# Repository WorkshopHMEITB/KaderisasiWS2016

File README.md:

# KaderisasiWS2016
###Repository untuk keperluan calon kru WS HME ITB 2016
1. **Informasi Umum**
  * Presentasi dan spesifikasi tugas tiap day dapat dilihat pada folder day yang bersesuaian
  * Pembagian kelompok beserta mentor-mentornya dapat dilihat [disini](https://github.com/WorkshopHMEITB/KaderisasiWS2016/blob/master/KelompokCakruWS2016.csv)
  * Kontak mentor dapat dilihat [disini](https://github.com/WorkshopHMEITB/KaderisasiWS2016/blob/master/KontakMentorCakruWS2016.csv)
2. **Aturan umum pengumpulan tugas**
  * Tugas yang sudah selesai harus dipresentasikan kepada mentor masing-masing kelompok pada waktu yang ditentukan bersama mentor sebelum batas waktu yang diberikan pada spesifikasi tugas
  * Tugas harus disertai dengan dokumentasi tugas menggunakan template dokumentasi yang ada pada repository KaderisasiWS2016
  * File-file terkait (yang akan diberitahu pada spesifikasi tiap tugas) beserta dokumentasinya harus dikumpulkan melalui repository KaderisasiWS2016 sebelum batas waktu yang diberikan pada spesifikasi tugas (cara pengumpulan tugas ke repository ada pada poin 3 file ini)
  * Telat mempresentasikan kepada mentor akan mengakibatkan pengurangan nilai total sebesar 5% (telat 1 hari), 15% (telat 2 hari), 30% (telat 3 hari), dan 50% (dengan kata lain tidak dianggap mengumpulkan jika telat lebih dari 4 hari)
3. **Cara pengumpulan tugas**<br  />
 1. Jika anda belum terdaftar di github, klik tombol ***Sign up*** di pojok kanan atas [page ini](https://github.com/WorkshopHMEITB/KaderisasiWS2016) dan ikuti terus prosedurnya hingga anda terdaftar
 2. Jika anda sudah terdaftar, *sign in* dengan menekan tombol ***Sign in*** di pojok kanan atas [page ini](https://github.com/WorkshopHMEITB/KaderisasiWS2016)
 3. Klik tombol ***Fork*** di pojok kanan atas [page ini](https://github.com/WorkshopHMEITB/KaderisasiWS2016)
 4. *Pop up window* akan muncul setelah anda menekan tombol *Fork*, tekan ***profil anda***.
 5. Sekarang, *repository* baru (yang merupakan *forked* repository [WorkshopHMEITB/KaderisasiWS2016](https://github.com/WorkshopHMEITB/KaderisasiWS2016)) akan muncul di profil anda. Alamat repository tersebut akan berbentuk seperti ini: https://github.com/USER_NAME/KaderisasiWS2016, sebagai contoh, https://github.com/fuad1502/KaderisasiWS2016. (Jika anda baru saja mem-*fork* repository WorkshopHMEITB/KaderisasiWS2016, anda akan langsung ter-*redirect* ke alamat repository baru anda tersebut)
 6. Setelah *forked repository* berhasil anda buat, anda dapat ***mengupload file-file*** yang harus anda upload ke repository tersebut. Cara mengupload file yang baik dan benar, ada pada bagian 4, "Cara mengupload file-file ke forked repository"
 7. Setelah semua file yang diperlukan sudah anda upload, tekan ***New Pull Request***
 8. Kemudian tekan tombol ***Create pull request***. Tuliskan "Tugas Day X Kelompok Y" pada bagian title dan tekan kembali tombol ***Create pull request***
 9. Selesai. Jika anda sudah mengupload semua file dengan benar, pihak kami akan menerima *pull request* anda dan menggabungkannya ke dalam repository [WorkshopHMEITB/KaderisasiWS2016](https://github.com/WorkshopHMEITB/KaderisasiWS2016)
4. **Cara mengupload file-file ke forked repository**
 1. Buka *forked repository* anda di https://github.com/USER_NAME/KaderisasiWS2016
 2. Buka folder day yang bersesuaian
 3. Buat folder pengumpulan tugas kelompok anda di dalam folder day tersebut dengan cara sebagai berikut
     * Tekan tombol ***Create new file***
     * Pada bagian "Name your file...", tulis "KelompokX" (ganti X dengan nomor kelompok anda), lalu tekan "/". Kemudian, tulis lagi ".gitkeep"
     * *Scroll* kebawah dan klik ***Commit new file***
 4. Pada folder pengumpulan tugas kelompok anda tersebut, klik tombol ***Upload files***
 5. Klik ***choose your files*** dan pilih file mana saja yang ingin anda upload
 6. Setelah semua file berhasil diupload, tekan tombol ***Commit changes***

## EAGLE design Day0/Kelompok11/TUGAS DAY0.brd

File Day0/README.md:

#Tugas Day 0
###*Template file dokumentasi belum ada, kerjakan saja file skematik dan PCB nya dahulu*
###*Tugas PCB file dan schematic file harus dikerjakan setiap anggota kelompok, namun PCB yang perlu dicetak hanya satu per kelompok*
1. **Detail Tugas**
  1. Membuat file skematik dari rangkaian di bawah ini menggunakan software Eagle<br  />
  
  2. Membuat file PCB dari skematik yang telah dibuat menggunakan software Eagle
  3. Mencetak 1 buah PCB dari file PCB yang telah dibuat
  4. Membeli komponen-komponen yang dibutuhkan dan memasangnya/menyoldernya pada PCB yang telah dicetak
  5. Membuat dan mengupload file dokumentasi ke folder yang sesuai di repository [KaderisasiWS2016](https://github.com/WorkshopHMEITB/KaderisasiWS2016) (caranya dapat dilihat pada file [README.md](https://github.com/WorkshopHMEITB/KaderisasiWS2016/blob/master/README.md) pada root directory repository)
  6. Mengupload file-file terkait ke folder yang sesuai di repository [KaderisasiWS2016](https://github.com/WorkshopHMEITB/KaderisasiWS2016). File-file yang dimaksud ialah sebagai berikut.
    * File Skematik
    * File PCB
2. **Parameter Penilaian**<br  />
Coming soon...
3. **Deadline**<br  />
Sabtu 17/9/2016 (Namun mengumpulkan minggu tidak dihitung telat satu hari untuk tugas ini, dikarenakan PCB tidak mungkin selesai hari minggu)
4. **Informasi Tambahan**
  * Software Eagle dapat didownload secara gratis sebagai *freeware* dari https://cadsoft.io/
  * Rangkaian yang diberikan diatas sulit untuk dimengerti dikarenakan pengintegrasian 4 komponen transistor dalam rangkaian kedalam satu IC CA3046. Berikut adalah gambar skematik rangkaian diatas apabila keempat transistor digambarkan satu per satu. <br  />
  
  * Tips untuk Mempermudah Pengerjaan
    * Manfaatkan fitur DRC pada pembuatan file PCB untuk memastikan desain yang anda buat dapat dicetak oleh tempat pencetakan anda
    * Gunakan ground plane untuk mempermudah routing (Tidak harus)
    * Gunakan IC header untuk memastikan IC tidak akan rusak saat proses penyolderan, serta agar IC dapat dilepas untuk dipakai dalam hal lain (Tidak harus)
    * Untuk mengurangi biaya mencetak PCB, ketika ingin mencetak, cetak PCB beberapa kelompok secara bersama-sama
    * Cetak maksimal 3 hari sebelum deadline jika pakai masking (Kamis, 15/9/2016), 2 hari jika tidak. Untuk jaga-jaga.
  * Informasi Pencetakan PCB
    * *Spectra* 
      * Lokasi : https://goo.gl/maps/9tBonaAyMZR2
      * Email : kng@bdg.centrin.net.id
      * Telepon : 022 - 7322667
      * Teknologi : Ukuran jalur minimum 0.2 mm (kalau mau aman 0.25 mm)
      * Dapat mencetak langsung ke tempatnya dengan membawa file PCB, atau dapat melalui email dan transfer ATM
    * *MultiKarya* 
      * Lokasi : https://goo.gl/maps/EgyCBrZe8uH2
      * Website : www.multikarya.com
      * Email : pcb_multikarya@yahoo.com
      * Telepon : 022 - 720 2852
      * Teknologi : lihat lengkapnya di http://www.multikarya.com/pcb_technical_indonesia.html
    * *Selc* 
      * Lokasi : https://goo.gl/maps/5XCbfng3uKE2
      * Website : www.selc-komponen.co.id
      * Email : selc@bdg.centrin.net.id
      * Telepon : 022 - 721 0909
      * Teknologi : lihat lengkapnya di http://www.selc-komponen.co.id/index.php?route=information/information&information_id=7)
  * Informasi Pembelian Komponen
    * *Anam* (https://goo.gl/maps/y4qWtzdkQtB2 sebelah Balubur Town Square)
    * *Jaya Plaza* (https://goo.gl/maps/nTADkQ1KY322)<br  />
    Jika kesulitan dalam menemukan CA3046, dapat ditemukan di toko i.want.electronics di Jaya Plaza dengan harga Rp. 27500
    * *Duta Irama* (https://goo.gl/maps/VzKpAT1tsW42 depan Jaya Plaza)
  * Jika ada pertanyaan silakan hubungi [mentor masing-masing](https://github.com/WorkshopHMEITB/KaderisasiWS2016/blob/master/KontakMentorCakruWS2016.csv)

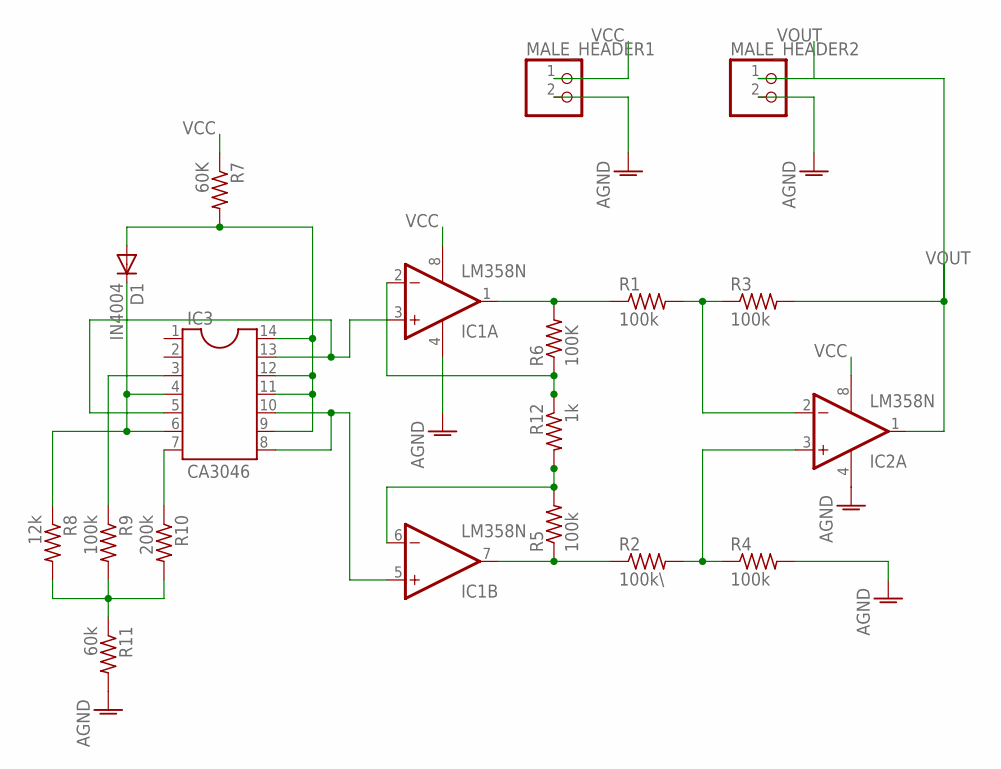
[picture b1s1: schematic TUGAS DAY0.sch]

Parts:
D1: IN4004; D-7.5
IC1, IC2: LM358N; DIL08
IC3: CA3046; DIL14
MALE_HEADER1, MALE_HEADER2: PINHD-1X2; 1X02
R1, R3, R4, R5, R9: 100k; 0207/7
R2: 100k\; 0207/7
R6: 100K; 0207/7
R7: 60K; 0207/7
R8: 12k; 0207/7
R10: 200k; 0207/7
R11: 60k; 0207/7
R12: 1k; 0207/7

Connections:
AGND: IC1.4 (V-), IC2.4 (V-), MALE_HEADER1.2, MALE_HEADER2.2, R4.2, R11.2
unnamed: IC1.6 (-IN), R5.2, R12.2
unnamed: D1.A, IC3.9, IC3.11, IC3.12, IC3.14, R7.2
unnamed: R8.2, R9.2, R10.2, R11.1
unnamed: IC3.7, R10.1
unnamed: IC3.3, R9.1
unnamed: D1.C, IC3.4, IC3.6, R8.1
unnamed: IC1.3 (+IN), IC3.5, IC3.13
unnamed: IC1.5 (+IN), IC3.8, IC3.10
unnamed: IC1.1 (OUT), R1.1, R6.2
unnamed: IC1.2 (-IN), R6.1, R12.1
unnamed: IC1.7 (OUT), R2.1, R5.1
unnamed: IC2.3 (+IN), R2.2, R4.1
unnamed: IC2.2 (-IN), R1.2, R3.1
VCC: IC1.8 (V+), IC2.8 (V+), MALE_HEADER1.1, R7.1
VOUT: IC2.1 (OUT), MALE_HEADER2.1, R3.2

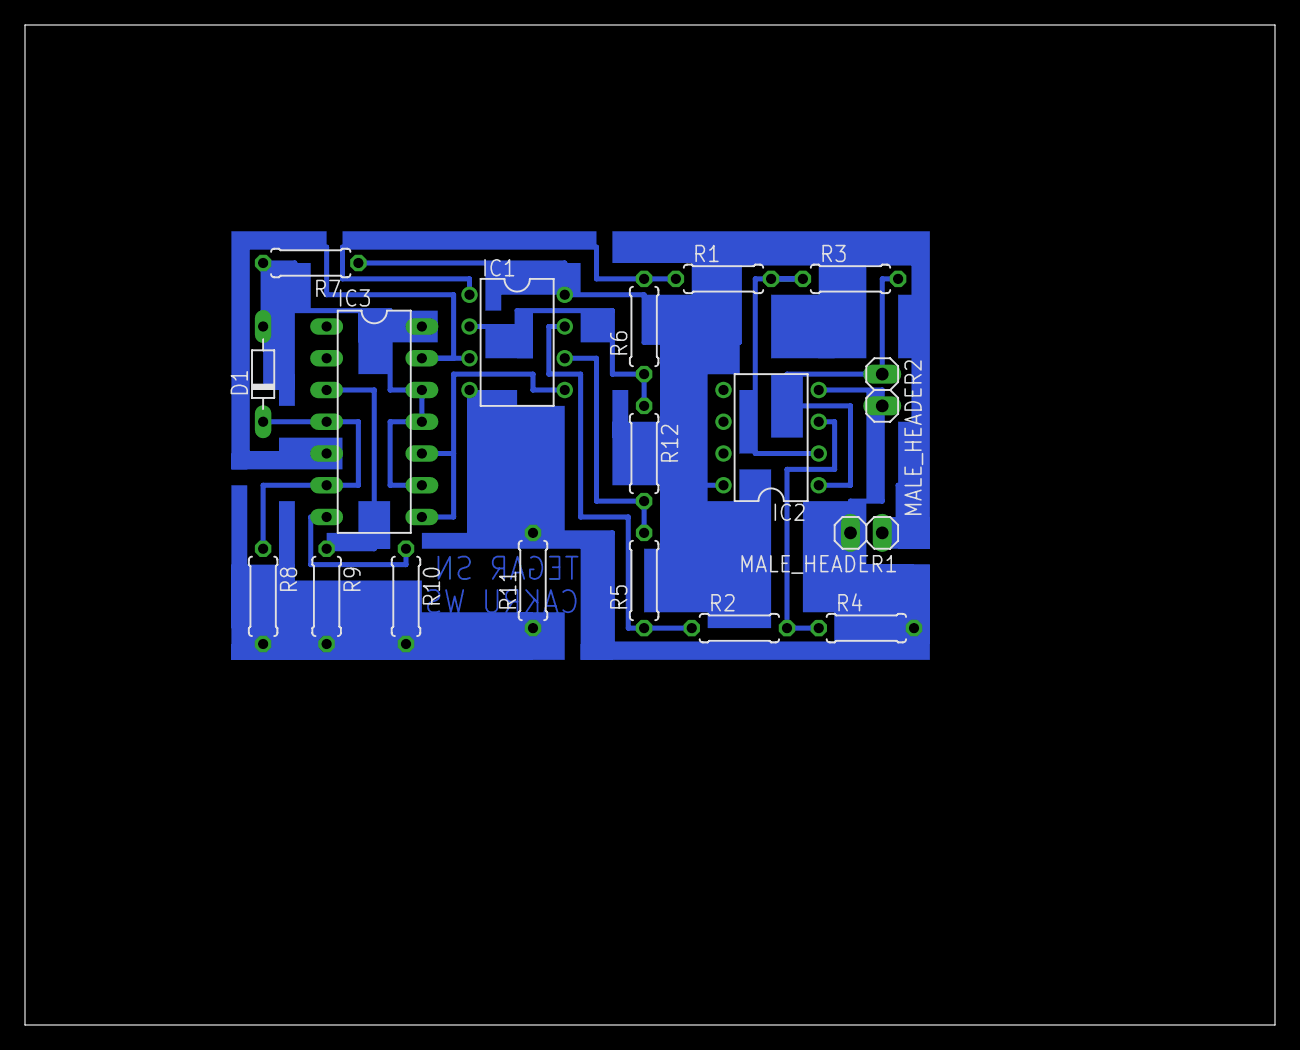
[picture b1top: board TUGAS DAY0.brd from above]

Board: 2 copper layers, 100.0 x 80.0 mm, 18 parts (0 on the bottom side), 16 nets.

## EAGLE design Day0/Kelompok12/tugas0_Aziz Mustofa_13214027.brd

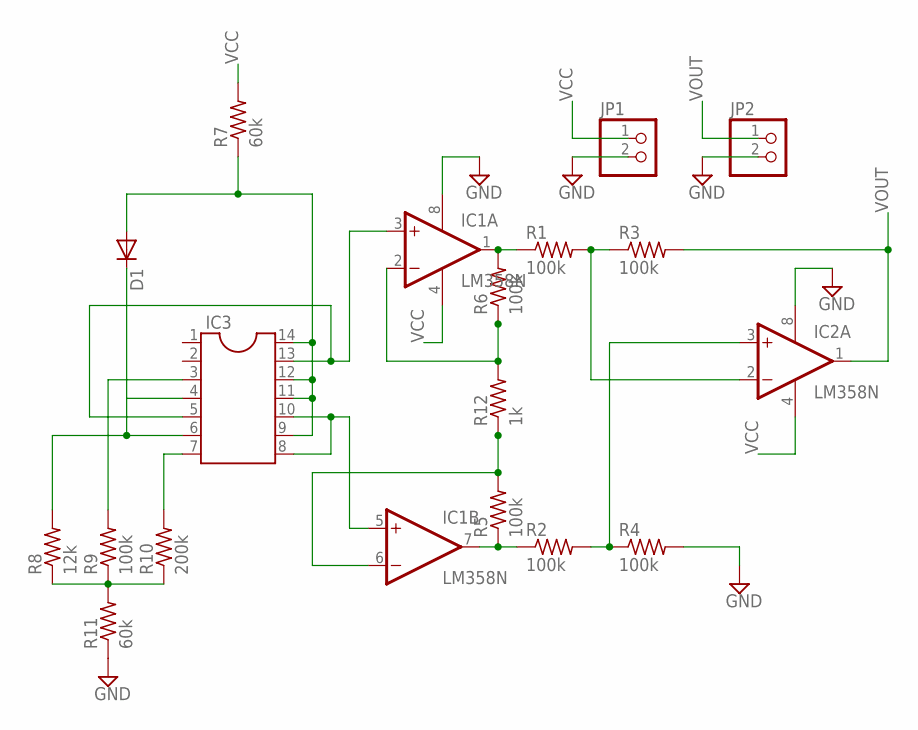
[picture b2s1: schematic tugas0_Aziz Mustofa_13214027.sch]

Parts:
D1: DIODE-D-7.5; D-7.5
IC1, IC2: LM358N; DIL08
IC3: DIL14
JP1, JP2: PINHD-1X2; 1X02
R1, R2, R3, R4, R5, R6, R9: 100k; 0204/7
R7, R11: 60k; 0204/7
R8: 12k; 0204/7
R10: 200k; 0204/7
R12: 1k; 0204/7

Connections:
GND: IC1.8 (V+), IC2.8 (V+), JP1.2, JP2.2, R4.2, R11.1
unnamed: IC1.6 (-IN), R5.2, R12.1
unnamed: D1.A, IC3.9, IC3.11, IC3.12, IC3.14, R7.1
unnamed: D1.C, IC3.4, IC3.6, R8.2
unnamed: R8.1, R9.1, R10.1, R11.2
unnamed: IC3.7, R10.2
unnamed: IC3.3, R9.2
unnamed: IC1.3 (+IN), IC3.5, IC3.13
unnamed: IC1.5 (+IN), IC3.8, IC3.10
unnamed: IC1.1 (OUT), R1.1, R6.2
unnamed: IC1.2 (-IN), R6.1, R12.2
unnamed: IC1.7 (OUT), R2.1, R5.1
unnamed: IC2.3 (+IN), R2.2, R4.1
unnamed: IC2.2 (-IN), R1.2, R3.1
VCC: JP1.1, R7.2
VOUT: IC2.1 (OUT), JP2.1, R3.2

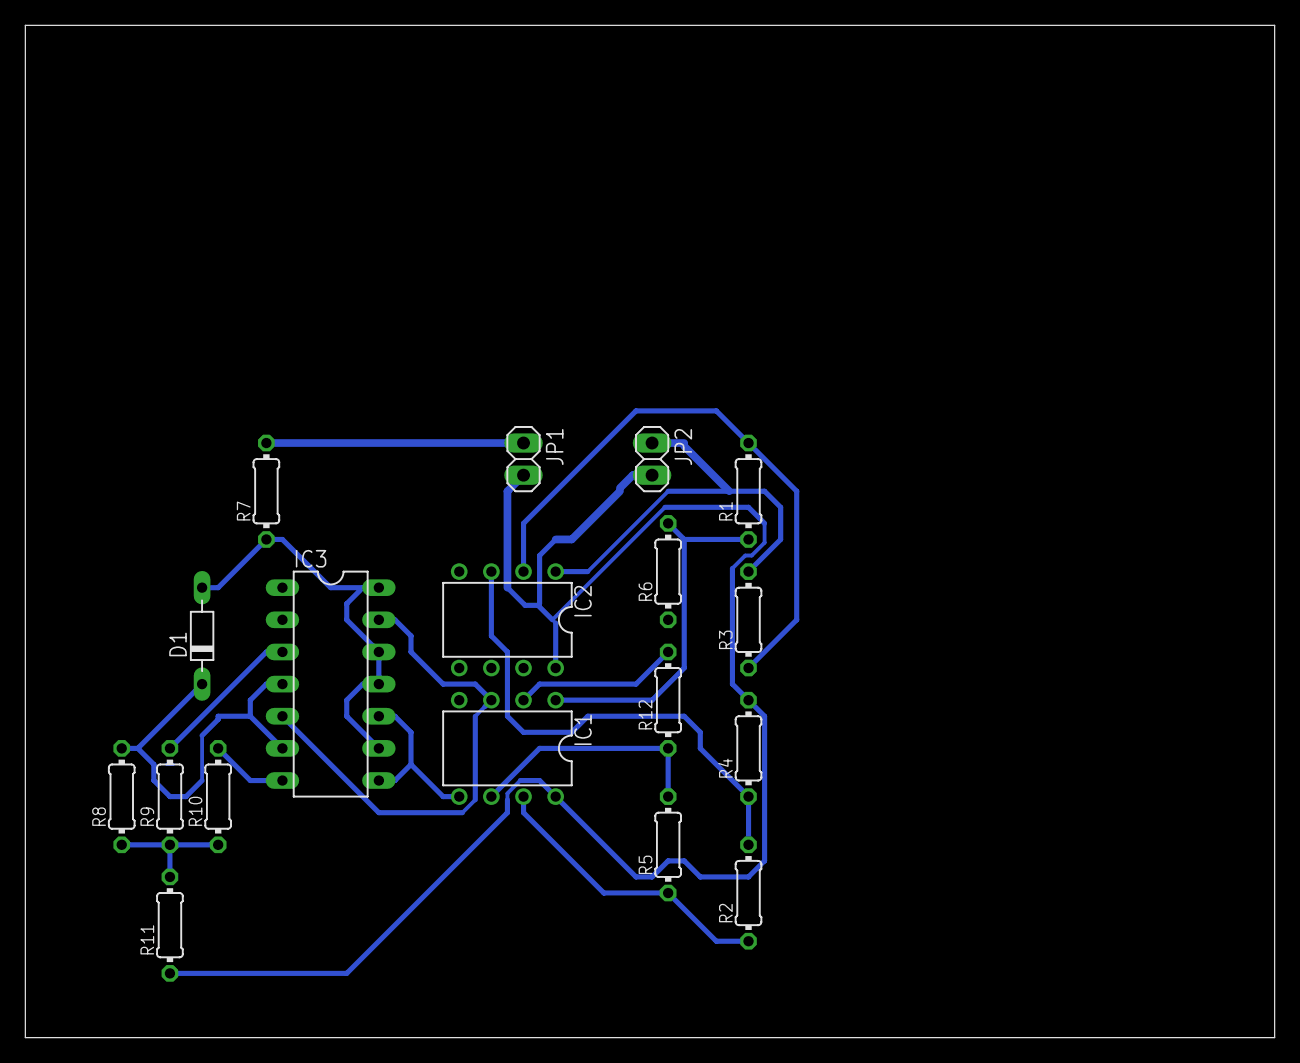
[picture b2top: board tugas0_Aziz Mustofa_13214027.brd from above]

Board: 2 copper layers, 98.7 x 80.0 mm, 18 parts (0 on the bottom side), 16 nets.

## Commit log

2016-09-24 Create Kelompok11
2016-10-01 Added premium features + I2C Screen
    - Pointer system
    - Increase or decrease
2016-10-01 Some fixes
2016-10-03 Running Text
2016-10-07 Major Changes
    - Add scrolling initialization text
    - Add flickering to scrolling text, preventing motion blur due to high LCD's persistence
    - Add 1602 LED configuration
    - Add serial input debugging
    - Fix increase and decrease minor yet troublesome bugs, where changing non-front digit won't loop through 0-9
2016-10-08 Kelompok11
2016-10-12 Create Kelompok3
